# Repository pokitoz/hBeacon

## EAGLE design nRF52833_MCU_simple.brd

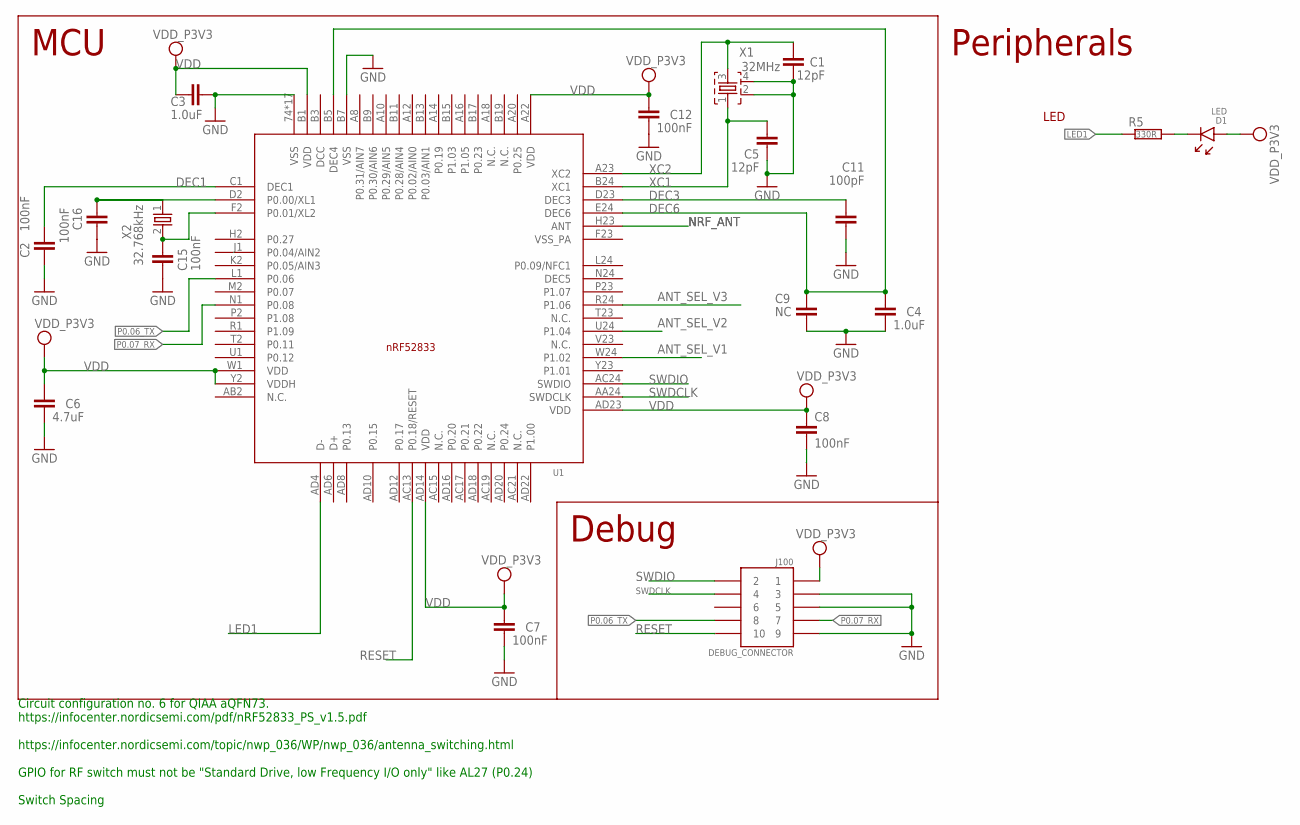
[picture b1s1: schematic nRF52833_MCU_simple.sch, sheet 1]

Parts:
C1, C5: 12pF; RESC0402_N
C2, C7, C8, C12, C15, C16: 100nF; RESC0402_N
C3, C4: 1.0uF; RESC0402_N
C6: 4.7uF; RESC0402_N
C9: NC; RESC0402_N
C11: 100pF; RESC0402_N
D1: LED; DIOC0603_N
J100: DEBUG_CONNECTOR; HDRV127P5X2-10_N
R5: 330R; RESC0402_N
U1: nRF52833-QIAA; AQFN50P700X700X85_HS-74N
X1: 32MHz; BT-XTAL_2016_N
X2: 32.768kHz; XTAL_3215_N

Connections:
ANT_SEL_V1: U1.W24 (P1.02)
ANT_SEL_V2: U1.U24 (P1.04)
ANT_SEL_V3: U1.R24 (P1.06)
DEC1: C2.1, U1.C1 (DEC1)
DEC3: C11.1, U1.D23 (DEC3)
DEC5: U1.N24 (DEC5)
DEC6: C4.1, C9.1, U1.B5 (DEC4), U1.E24 (DEC6)
GND: C1.2, C2.2, C3.2, C4.2, C5.2, C6.2, C7.2, C8.2, C9.2, C11.2, C12.2, C15.1, C16.1, J100.3, J100.5, J100.9, U1.74 (VSS), U1.B7 (VSS), U1.P$1 (VSS), U1.P$2 (VSS), U1.P$3 (VSS), U1.P$4 (VSS), U1.P$5 (VSS), U1.P$10 (VSS), U1.P$11 (VSS), U1.P$12 (VSS), U1.P$13 (VSS), U1.P$14 (VSS), U1.P$15 (VSS), U1.P$16 (VSS), U1.P$17 (VSS), U1.P$18 (VSS), U1.P$19 (VSS), U1.P$20 (VSS), X1.2, X1.4; also elsewhere on the board
LED1: R5.1, U1.AD4 (D-)
unnamed: C16.2, U1.D2 (P0.00/XL1), X2.1
unnamed: C15.2, U1.F2 (P0.01/XL2), X2.2
unnamed: D1.1 (C), R5.2
NRF_ANT: U1.H23 (ANT); also elsewhere on the board
P0.06_TX: J100.8, U1.L1 (P0.06)
P0.07_RX: J100.7, U1.N1 (P0.08)
RESET: J100.10, U1.AC13 (P0.18/RESET)
SWDCLK: J100.4, U1.AA24 (SWDCLK)
SWDIO: J100.2, U1.AC24 (SWDIO)
VDD: C3.1, C6.1, C7.1, C8.1, C12.1, D1.2 (A), J100.1, U1.A22 (VDD), U1.AD14 (VDD), U1.AD23 (VDD), U1.B1 (VDD), U1.W1 (VDD), U1.Y2 (VDDH); also elsewhere on the board
VSS_PA: U1.F23 (VSS_PA)
XC1: C5.1, U1.B24 (XC1), X1.1
XC2: C1.1, U1.A23 (XC2), X1.3

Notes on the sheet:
Circuit configuration no. 6 for QIAA aQFN73. https://infocenter.nordicsemi.com/pdf/nRF52833_PS_v1.5.pdf https://infocenter.nordicsemi.com/topic/nwp_036/WP/nwp_036/antenna_switching.html GPIO for RF switch must not be "Standard Drive, low Frequency I/O only" like AL27 (P0.24) Switch Spacing
MCU
Debug
Peripherals
LED

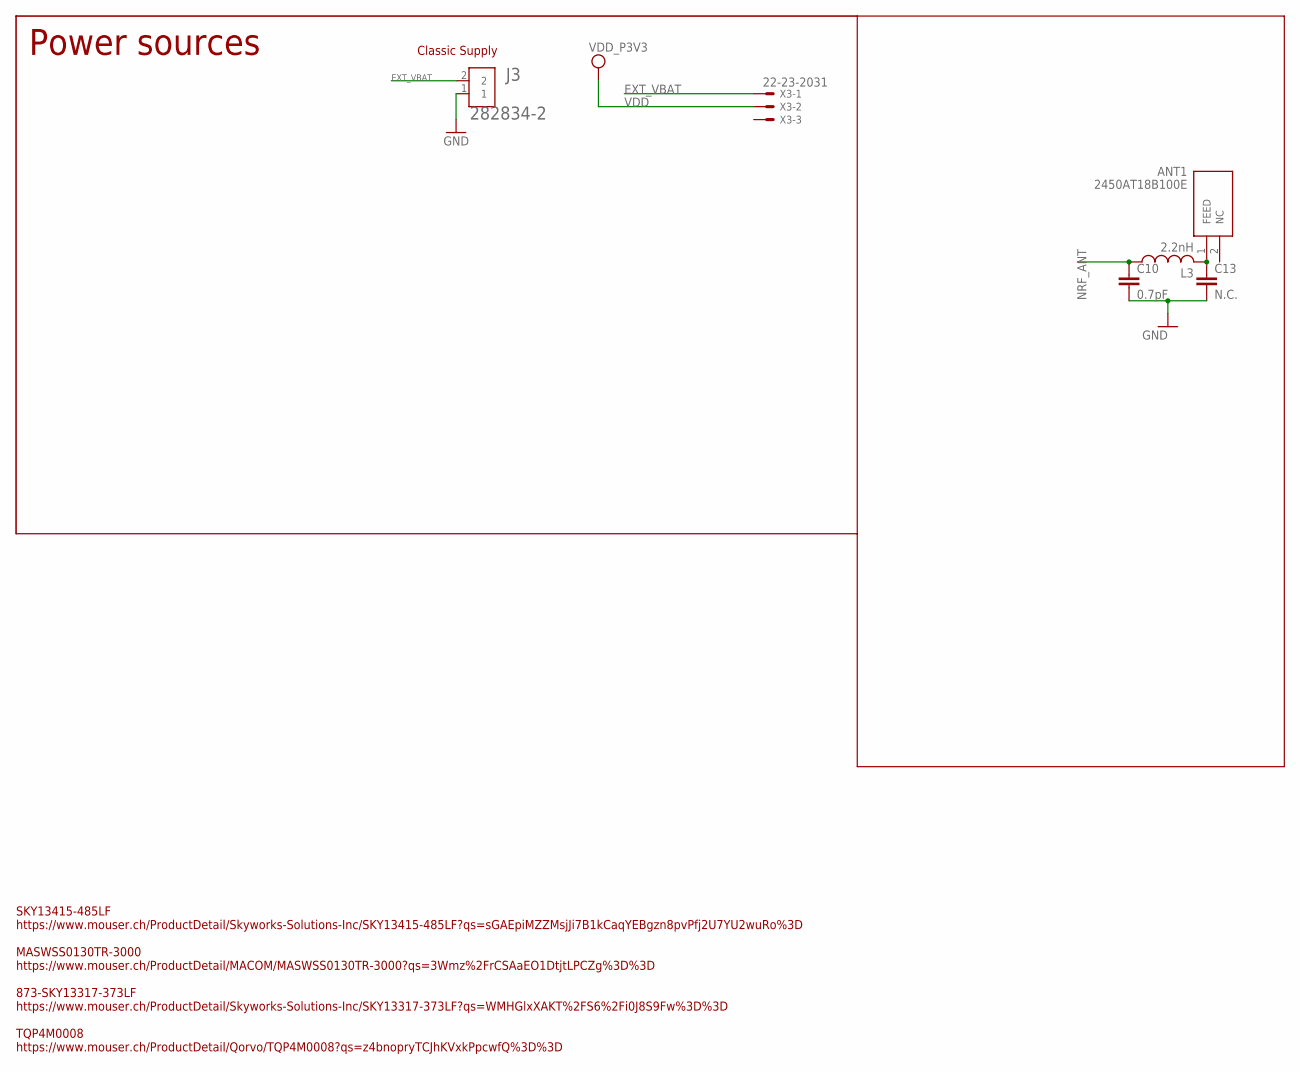
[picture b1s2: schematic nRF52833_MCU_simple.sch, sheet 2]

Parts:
ANT1: 2450AT18B100E; ANTC3216X140N
C10: 0.7pF; RESC0402_N
C13: N.C.; RESC0402_N
J3: 282834-2; CONN_282834-2
L3: 2.2nH; RESC0402_N
X3: 22-23-2031

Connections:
EXT_VBAT: J3.2, X3.1
GND: C10.2, C13.2, J3.1; also elsewhere on the board
unnamed: ANT1.1 (FEED), C13.1, L3.2
NRF_ANT: C10.1, L3.1; also elsewhere on the board
VDD: X3.2; also elsewhere on the board

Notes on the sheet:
Power sources
SKY13415-485LF https://www.mouser.ch/ProductDetail/Skyworks-Solutions-Inc/SKY13415-485LF?qs=sGAEpiMZZMsjJi7B1kCaqYEBgzn8pvPfj2U7YU2wuRo%3D MASWSS0130TR-3000 https://www.mouser.ch/ProductDetail/MACOM/MASWSS0130TR-3000?qs=3Wmz%2FrCSAaEO1DtjtLPCZg%3D%3D 873-SKY13317-373LF https://www.mouser.ch/Product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
Classic Supply

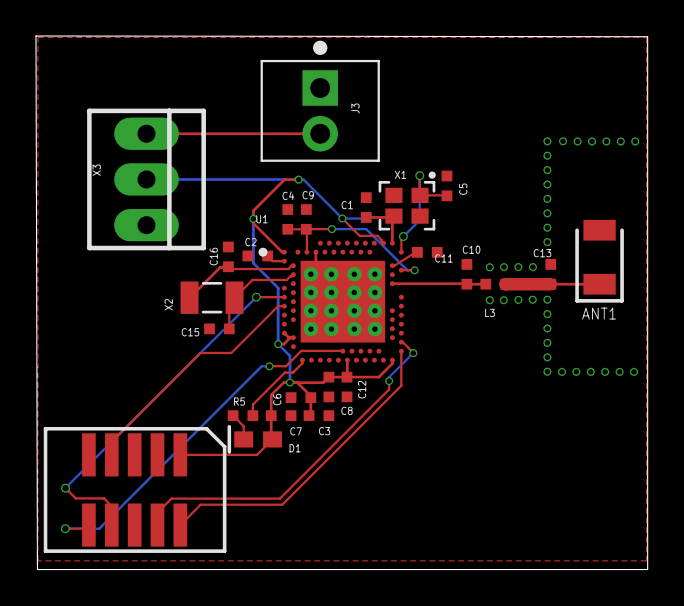
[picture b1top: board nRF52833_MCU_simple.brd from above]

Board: 2 copper layers, 34.0 x 29.6 mm, 25 parts (0 on the bottom side), 19 nets.

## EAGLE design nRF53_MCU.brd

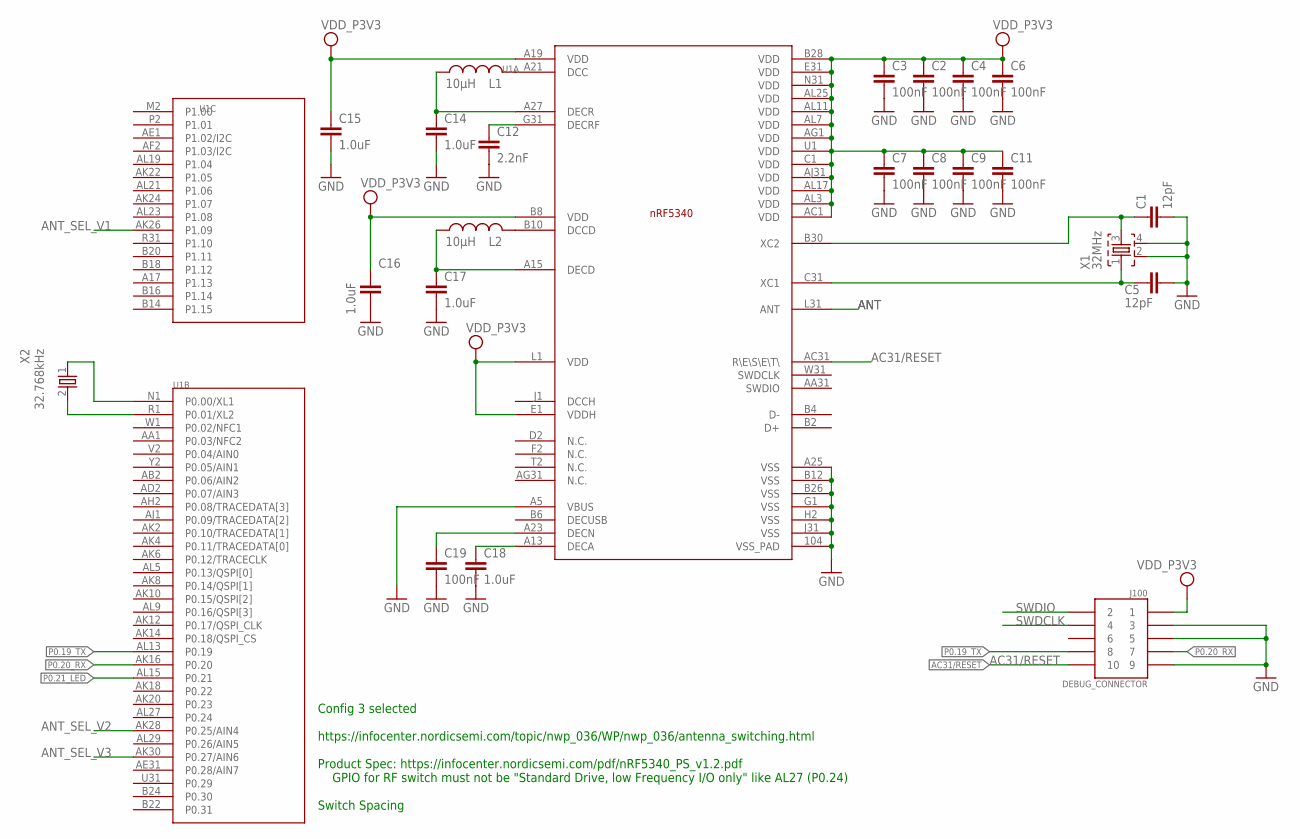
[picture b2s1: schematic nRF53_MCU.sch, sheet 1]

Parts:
C1, C5: 12pF; RESC0402_N
C2, C3, C4, C6, C7, C8, C9, C11, C19: 100nF; RESC0402_N
C12: 2.2nF; RESC0402_N
C14, C15, C16, C17, C18: 1.0uF; RESC0402_N
J100: DEBUG_CONNECTOR; HDRV127P5X2-10_N
L1, L2: 10µH; RESC0603_N
U1: nRF5340-QKAA; AQFN40P700X700X85_HS-99N
X1: 32MHz; BT-XTAL_2016_N
X2: 32.768kHz; XTAL_3215_N

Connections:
AC31/RESET: J100.10, U1.AC31 (R\E\S\E\T\)
ANT: U1.L31 (ANT); also elsewhere on the board
ANT_SEL_V1: U1.AK26 (P1.09); also elsewhere on the board
ANT_SEL_V2: U1.AK28 (P0.25/AIN4); also elsewhere on the board
ANT_SEL_V3: U1.AK30 (P0.27/AIN6); also elsewhere on the board
DCCH: U1.J1 (DCCH)
DECUSB: U1.B6 (DECUSB)
GND: C1.2, C2.2, C3.2, C4.2, C5.2, C6.2, C7.2, C8.2, C9.2, C11.2, C12.2, C14.2, C15.2, C16.2, C17.2, C18.2, C19.2, J100.3, J100.5, J100.9, U1.104 (VSS_PAD), U1.A5 (VBUS), U1.A25 (VSS), U1.B12 (VSS), U1.B26 (VSS), U1.G1 (VSS), U1.H2 (VSS), U1.J31 (VSS), X1.2, X1.4; also elsewhere on the board
unnamed: L2.2, U1.B10 (DCCD)
unnamed: C1.1, U1.B30 (XC2), X1.3
unnamed: C14.1, L1.1, U1.A27 (DECR)
unnamed: L1.2, U1.A21 (DCC)
unnamed: C18.1, U1.A13 (DECA)
unnamed: C17.1, L2.1, U1.A15 (DECD)
unnamed: C12.1, U1.G31 (DECRF)
unnamed: C19.1, U1.A23 (DECN)
unnamed: C5.1, U1.C31 (XC1), X1.1
unnamed: U1.N1 (P0.00/XL1), X2.1
unnamed: U1.R1 (P0.01/XL2), X2.2
P0.19_TX: J100.8, U1.AL13 (P0.19)
P0.20_RX: J100.7, U1.AK16 (P0.20)
P0.21_LED: U1.AL15 (P0.21); also elsewhere on the board
SWDCLK: J100.4
SWDIO: J100.2
VCC: C2.1, C3.1, C4.1, C6.1, C7.1, C8.1, C9.1, C11.1, C15.1, C16.1, U1.A19 (VDD), U1.AC1 (VDD), U1.AG1 (VDD), U1.AJ31 (VDD), U1.AL3 (VDD), U1.AL7 (VDD), U1.AL11 (VDD), U1.AL17 (VDD), U1.AL25 (VDD), U1.B8 (VDD), U1.B28 (VDD), U1.C1 (VDD), U1.E1 (VDDH), U1.E31 (VDD), U1.L1 (VDD), U1.N31 (VDD), U1.U1 (VDD)
VDD_P3V3: J100.1; also elsewhere on the board

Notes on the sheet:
Config 3 selected https://infocenter.nordicsemi.com/topic/nwp_036/WP/nwp_036/antenna_switching.html Product Spec: https://infocenter.nordicsemi.com/pdf/nRF5340_PS_v1.2.pdf GPIO for RF switch must not be "Standard Drive, low Frequency I/O only" like AL27 (P0.24) Switch Spacing

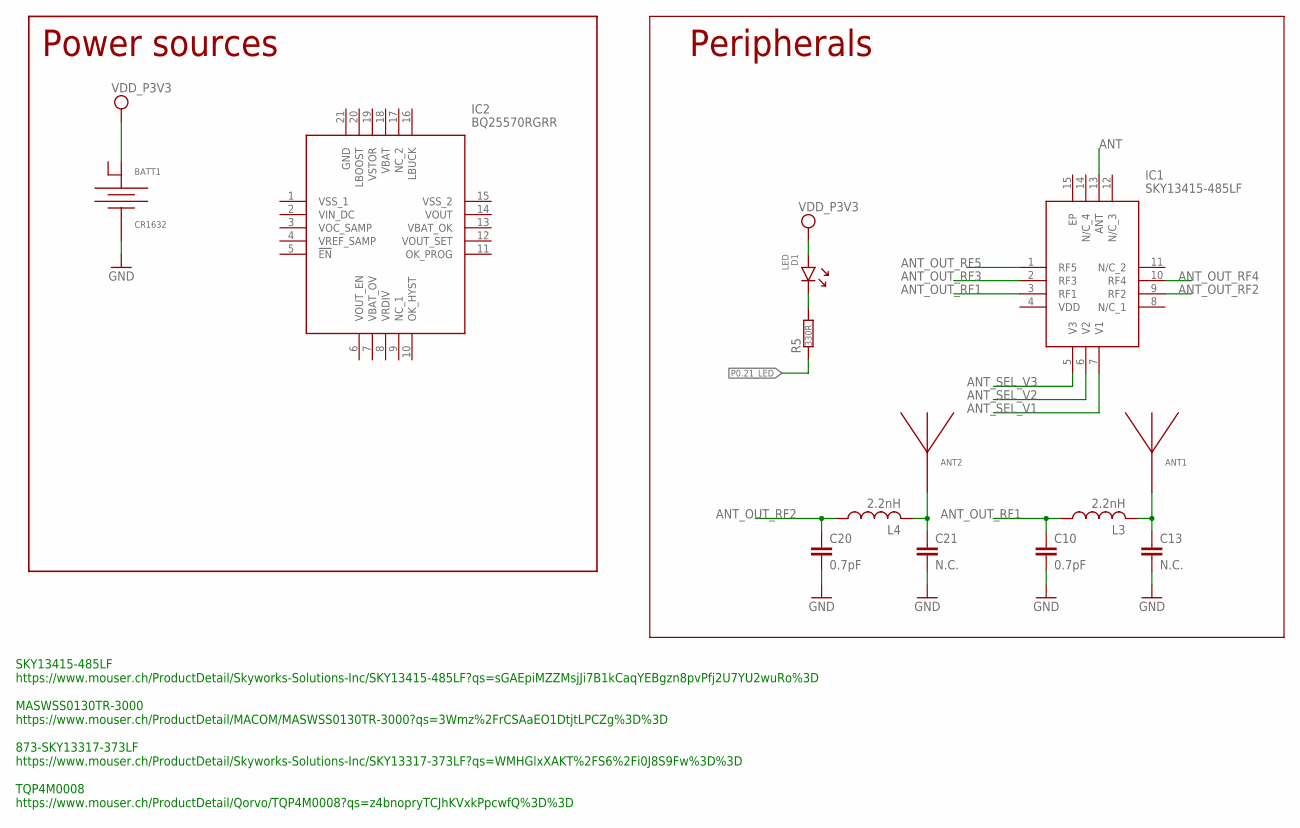
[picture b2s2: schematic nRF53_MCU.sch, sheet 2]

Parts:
ANT1, ANT2: ANTENNA_QUARTER-WAVE_MONOPOLE_MEANDERED_LEFT; QWMP_MEANDERED_LEFT_+6
BATT1: CR1632; CR1632_HOLDER_TH
C10, C20: 0.7pF; RESC0402_N
C13, C21: N.C.; RESC0402_N
D1: LED; DIOC0603_N
IC1: SKY13415-485LF; SKY13415485LF
IC2: BQ25570RGRR; QFN50P350X350X100-21N
L3, L4: 2.2nH; RESC0402_N
R5: 330R; RESC0402_N

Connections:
ANT: IC1.13 (ANT); also elsewhere on the board
ANT_OUT_RF1: C10.1, IC1.3 (RF1), L3.1
ANT_OUT_RF2: C20.1, IC1.9 (RF2), L4.1
ANT_OUT_RF3: IC1.2 (RF3)
ANT_OUT_RF4: IC1.10 (RF4)
ANT_OUT_RF5: IC1.1 (RF5)
ANT_SEL_V1: IC1.7 (V1); also elsewhere on the board
ANT_SEL_V2: IC1.6 (V2); also elsewhere on the board
ANT_SEL_V3: IC1.5 (V3); also elsewhere on the board
GND: BATT1.1 (-), C10.2, C13.2, C20.2, C21.2; also elsewhere on the board
unnamed: ANT1.P$1, C13.1, L3.2
unnamed: D1.1 (C), R5.2
unnamed: ANT2.P$1, C21.1, L4.2
P0.21_LED: R5.1; also elsewhere on the board
VDD_P3V3: BATT1.2 (+), D1.2 (A); also elsewhere on the board

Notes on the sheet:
Power sources
Peripherals
SKY13415-485LF https://www.mouser.ch/ProductDetail/Skyworks-Solutions-Inc/SKY13415-485LF?qs=sGAEpiMZZMsjJi7B1kCaqYEBgzn8pvPfj2U7YU2wuRo%3D MASWSS0130TR-3000 https://www.mouser.ch/ProductDetail/MACOM/MASWSS0130TR-3000?qs=3Wmz%2FrCSAaEO1DtjtLPCZg%3D%3D 873-SKY13317-373LF https://www.mouser.ch/Product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

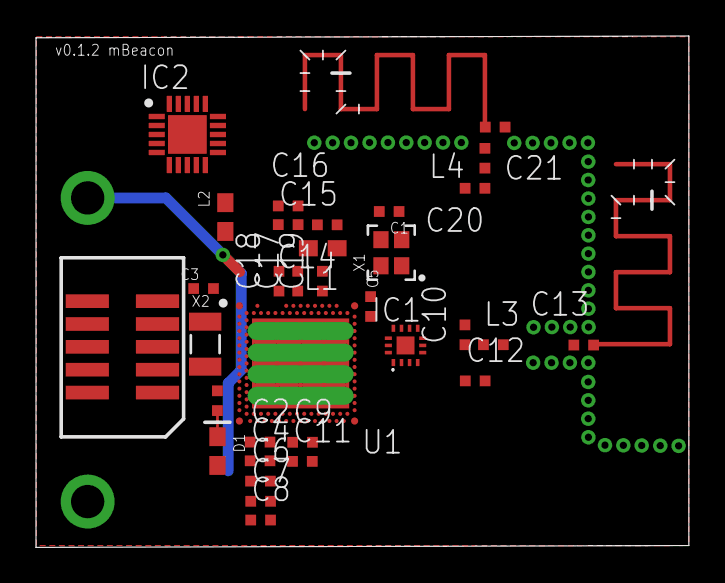
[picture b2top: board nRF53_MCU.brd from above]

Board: 2 copper layers, 36.3 x 28.4 mm, 36 parts (1 on the bottom side), 27 nets.

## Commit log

2022-03-22 Add base files
2022-03-24 Added nrf53 board with 2 antennas
2022-03-25 Restart with nrf 52833
2022-03-25 Add gpios for nrf52833
2022-03-25 Add capa for option 3 nrf52833
2022-03-26 Redefine schematic to add energy harvest
2022-03-26 Add doc for devices used
2022-03-26 Separate the power and the antennas
2022-03-26 Rastness applied
2022-03-27 Schematic: Move devices
2022-03-27 Schematic pdf
2022-04-02 Add the 5 antennas
2022-04-02 Fix errors
2022-04-19 Routing the antennas
2022-05-07 Add links for harvestors
2022-05-26 Add pcb trace antenna 0.7mm
2022-05-26 Add 0.7mm signal
2022-05-26 Create Stuff
2022-06-27 GND via for antenna signal
2022-09-11 Fix warnings
2022-09-14 Fix pad/signal spacing issue
2022-09-16 Disconnect reset
2022-09-24 Reduce signal size
2022-09-24 Increase some signal size
2022-09-24 Make sure to respect the design rules
2022-11-08 Manufactured tag
2023-06-18 Add basic files for nrf52833
